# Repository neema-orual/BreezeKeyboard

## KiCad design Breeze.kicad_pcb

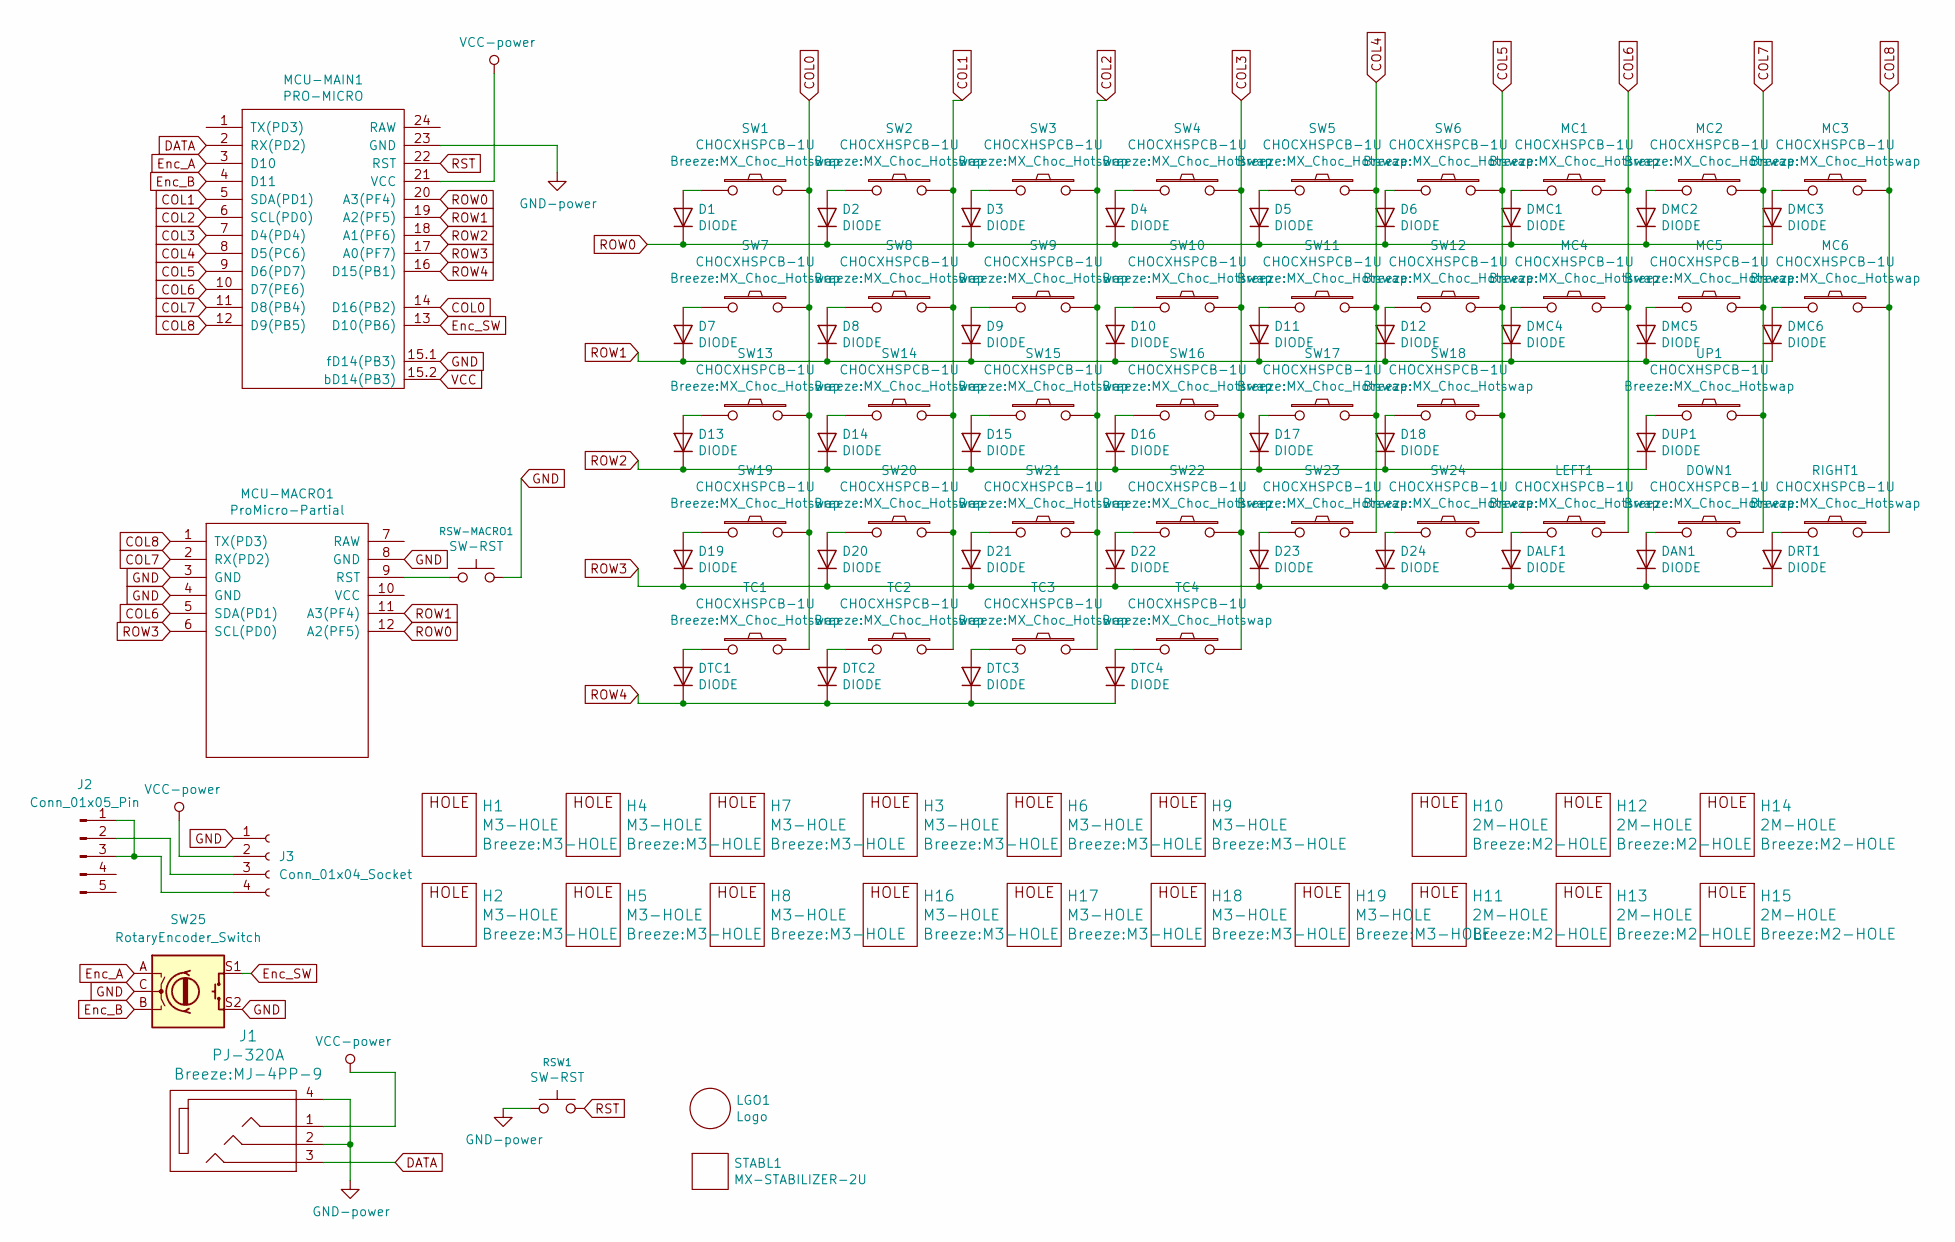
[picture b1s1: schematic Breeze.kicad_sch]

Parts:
D1, D2, D3, D4, D5, D6, D7, D8, D9, D10, D11, D12, D13, D14, D15, D16, D17, D18, D19, D20, D21, D22, D23, D24: DIODE; SOD-123FL; LCSC C64898
DALF1: DIODE; SOD-123FL; LCSC C64898
DAN1: DIODE; SOD-123FL; LCSC C64898
DMC1, DMC2, DMC3, DMC4, DMC5, DMC6: DIODE; SOD-123FL; LCSC C64898
DOWN1: CHOCXHSPCB-1U; MX_Choc_Hotswap
DRT1: DIODE; SOD-123FL; LCSC C64898
DTC1, DTC2, DTC3, DTC4: DIODE; SOD-123FL; LCSC C64898
DUP1: DIODE; SOD-123FL; LCSC C64898
H1, H2, H3, H4, H5, H6, H7, H8, H9, H16, H17, H18, H19: M3-HOLE
H10, H11, H12, H13, H14, H15: 2M-HOLE; M2-HOLE
J1: PJ-320A; MJ-4PP-9
J2: Conn_01x05_Pin; PinHeader_1x05_P2.54mm_Vertical
J3: Conn_01x04_Socket; PinHeader_1x04_P2.54mm_Vertical
LEFT1: CHOCXHSPCB-1U; MX_Choc_Hotswap
LGO1: Logo; logo
MC1, MC2, MC3, MC4, MC5, MC6: CHOCXHSPCB-1U; MX_Choc_Hotswap
MCU-MACRO1: ProMicro-Partial; PROMICRO-PARTIAL2
MCU-MAIN1: PRO-MICRO; ProMicro
RIGHT1: CHOCXHSPCB-1U; MX_Choc_Hotswap
RSW1: SW-RST; TACT_SWITCH_TVBP06
RSW-MACRO1: SW-RST; TACT_SWITCH_TVBP06
STABL1: MX-STABILIZER-2U; Stabilizer_MX_2u
SW1, SW2, SW3, SW4, SW5, SW6, SW7, SW8, SW9, SW10, SW11, SW12, SW13, SW14, SW15, SW16, SW17, SW18, SW19, SW20, SW21, SW22, SW23, SW24: CHOCXHSPCB-1U; MX_Choc_Hotswap
SW25: RotaryEncoder_Switch; RotaryEncoder_Alps_EC11E-Switch_Vertical_H20mm
TC1, TC2, TC3, TC4: CHOCXHSPCB-1U; MX_Choc_Hotswap
UP1: CHOCXHSPCB-1U; MX_Choc_Hotswap

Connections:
COL0: MCU-MAIN1.14 (D16(PB2)), SW1.2, SW7.2, SW13.2, SW19.2, TC1.2
COL1: MCU-MAIN1.5 (SDA(PD1)), SW2.2, SW8.2, SW14.2, SW20.2, TC2.2
COL2: MCU-MAIN1.6 (SCL(PD0)), SW3.2, SW9.2, SW15.2, SW21.2, TC3.2
COL3: MCU-MAIN1.7 (D4(PD4)), SW4.2, SW10.2, SW16.2, SW22.2, TC4.2
COL4: MCU-MAIN1.8 (D5(PC6)), SW5.2, SW11.2, SW17.2, SW23.2
COL5: MCU-MAIN1.9 (D6(PD7)), SW6.2, SW12.2, SW18.2, SW24.2
COL6: LEFT1.2, MC1.2, MC4.2, MCU-MACRO1.5 (SDA(PD1)), MCU-MAIN1.10 (D7(PE6))
COL7: DOWN1.2, MC2.2, MC5.2, MCU-MACRO1.2 (RX(PD2)), MCU-MAIN1.11 (D8(PB4)), UP1.2
COL8: MC3.2, MC6.2, MCU-MACRO1.1 (TX(PD3)), MCU-MAIN1.12 (D9(PB5)), RIGHT1.2
DATA: J1.3, MCU-MAIN1.2 (RX(PD2))
Enc_A: MCU-MAIN1.3 (D10), SW25.A
Enc_B: MCU-MAIN1.4 (D11), SW25.B
Enc_SW: MCU-MAIN1.13 (D10(PB6)), SW25.S1
unnamed: D1.2 (A), SW1.1
unnamed: D2.2 (A), SW2.1
unnamed: D3.2 (A), SW3.1
unnamed: D4.2 (A), SW4.1
unnamed: D5.2 (A), SW5.1
unnamed: D6.2 (A), SW6.1
unnamed: D7.2 (A), SW7.1
unnamed: D8.2 (A), SW8.1
unnamed: D9.2 (A), SW9.1
unnamed: D10.2 (A), SW10.1
unnamed: D11.2 (A), SW11.1
unnamed: D12.2 (A), SW12.1
unnamed: D13.2 (A), SW13.1
unnamed: D14.2 (A), SW14.1
unnamed: D15.2 (A), SW15.1
unnamed: D16.2 (A), SW16.1
unnamed: D17.2 (A), SW17.1
unnamed: D18.2 (A), SW18.1
unnamed: D19.2 (A), SW19.1
unnamed: D20.2 (A), SW20.1
unnamed: D21.2 (A), SW21.1
unnamed: D22.2 (A), SW22.1
unnamed: D23.2 (A), SW23.1
unnamed: D24.2 (A), SW24.1
unnamed: DALF1.2 (A), LEFT1.1
unnamed: DAN1.2 (A), DOWN1.1
unnamed: DMC1.2 (A), MC1.1
unnamed: DMC2.2 (A), MC2.1
unnamed: DMC3.2 (A), MC3.1
unnamed: DMC4.2 (A), MC4.1
unnamed: DMC5.2 (A), MC5.1
unnamed: DMC6.2 (A), MC6.1
unnamed: DRT1.2 (A), RIGHT1.1
unnamed: DTC1.2 (A), TC1.1
unnamed: DTC2.2 (A), TC2.1
unnamed: DTC3.2 (A), TC3.1
unnamed: DTC4.2 (A), TC4.1
unnamed: DUP1.2 (A), UP1.1
unnamed: J2.1, J2.3, J3.4
unnamed: J2.2, J3.3
unnamed: MCU-MACRO1.9 (RST), RSW-MACRO1.1
ROW0: D1.1 (K), D2.1 (K), D3.1 (K), D4.1 (K), D5.1 (K), D6.1 (K), DMC1.1 (K), DMC2.1 (K), DMC3.1 (K), MCU-MACRO1.12 (A2(PF5)), MCU-MAIN1.20 (A3(PF4))
ROW1: D7.1 (K), D8.1 (K), D9.1 (K), D10.1 (K), D11.1 (K), D12.1 (K), DMC4.1 (K), DMC5.1 (K), DMC6.1 (K), MCU-MACRO1.11 (A3(PF4)), MCU-MAIN1.19 (A2(PF5))
ROW2: D13.1 (K), D14.1 (K), D15.1 (K), D16.1 (K), D17.1 (K), D18.1 (K), DUP1.1 (K), MCU-MAIN1.18 (A1(PF6))
ROW3: D19.1 (K), D20.1 (K), D21.1 (K), D22.1 (K), D23.1 (K), D24.1 (K), DALF1.1 (K), DAN1.1 (K), DRT1.1 (K), MCU-MACRO1.6 (SCL(PD0)), MCU-MAIN1.17 (A0(PF7))
ROW4: DTC1.1 (K), DTC2.1 (K), DTC3.1 (K), DTC4.1 (K), MCU-MAIN1.16 (D15(PB1))
RST: MCU-MAIN1.22 (RST), RSW1.2

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
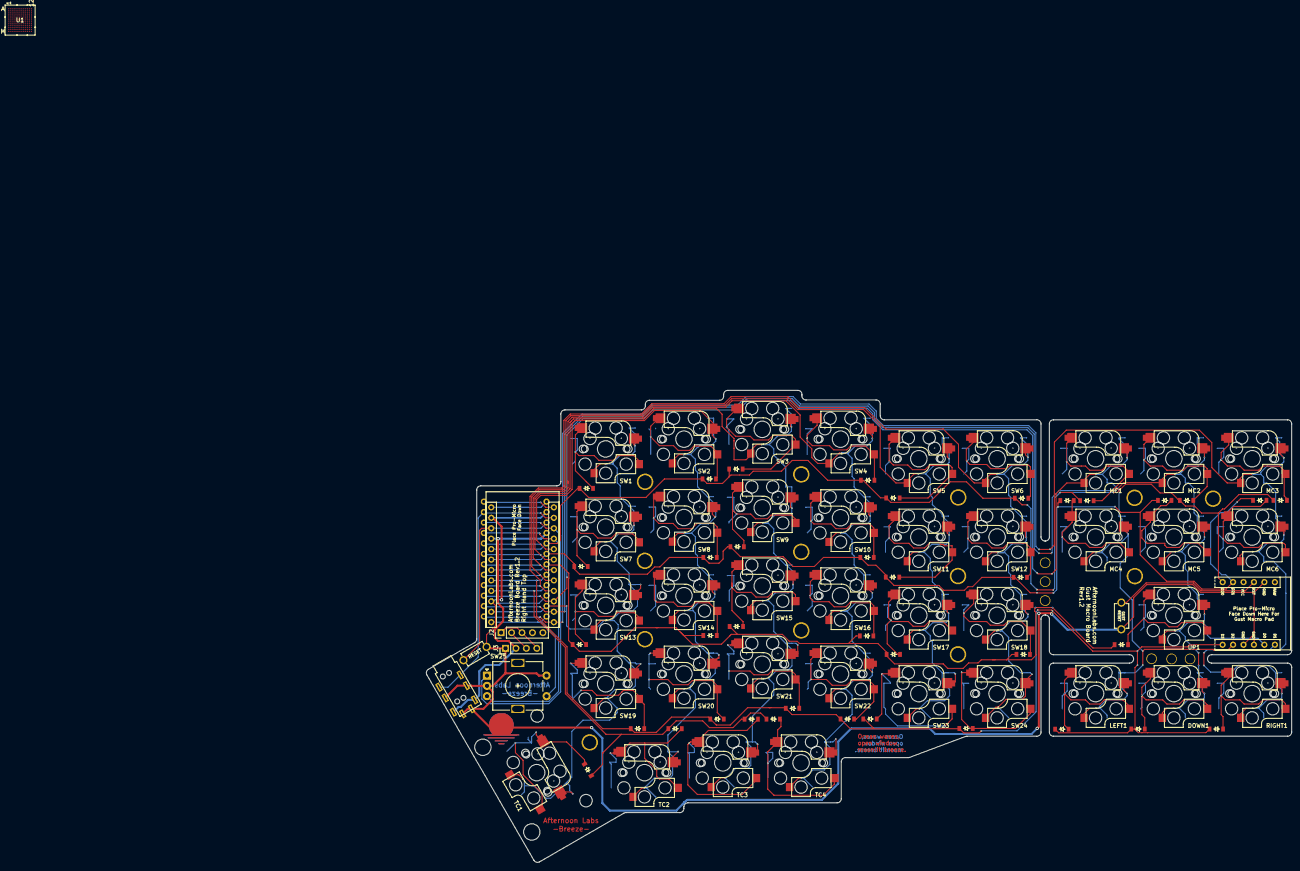
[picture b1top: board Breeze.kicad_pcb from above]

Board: 2 copper layers, 210.6 x 114.9 mm, 106 parts (0 on the bottom side), 62 nets.

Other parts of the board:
U1: STM32H723ZGI6; UFBGA-144_7X7_STM

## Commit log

2024-01-21 added encoder and oled display via elite-pi
